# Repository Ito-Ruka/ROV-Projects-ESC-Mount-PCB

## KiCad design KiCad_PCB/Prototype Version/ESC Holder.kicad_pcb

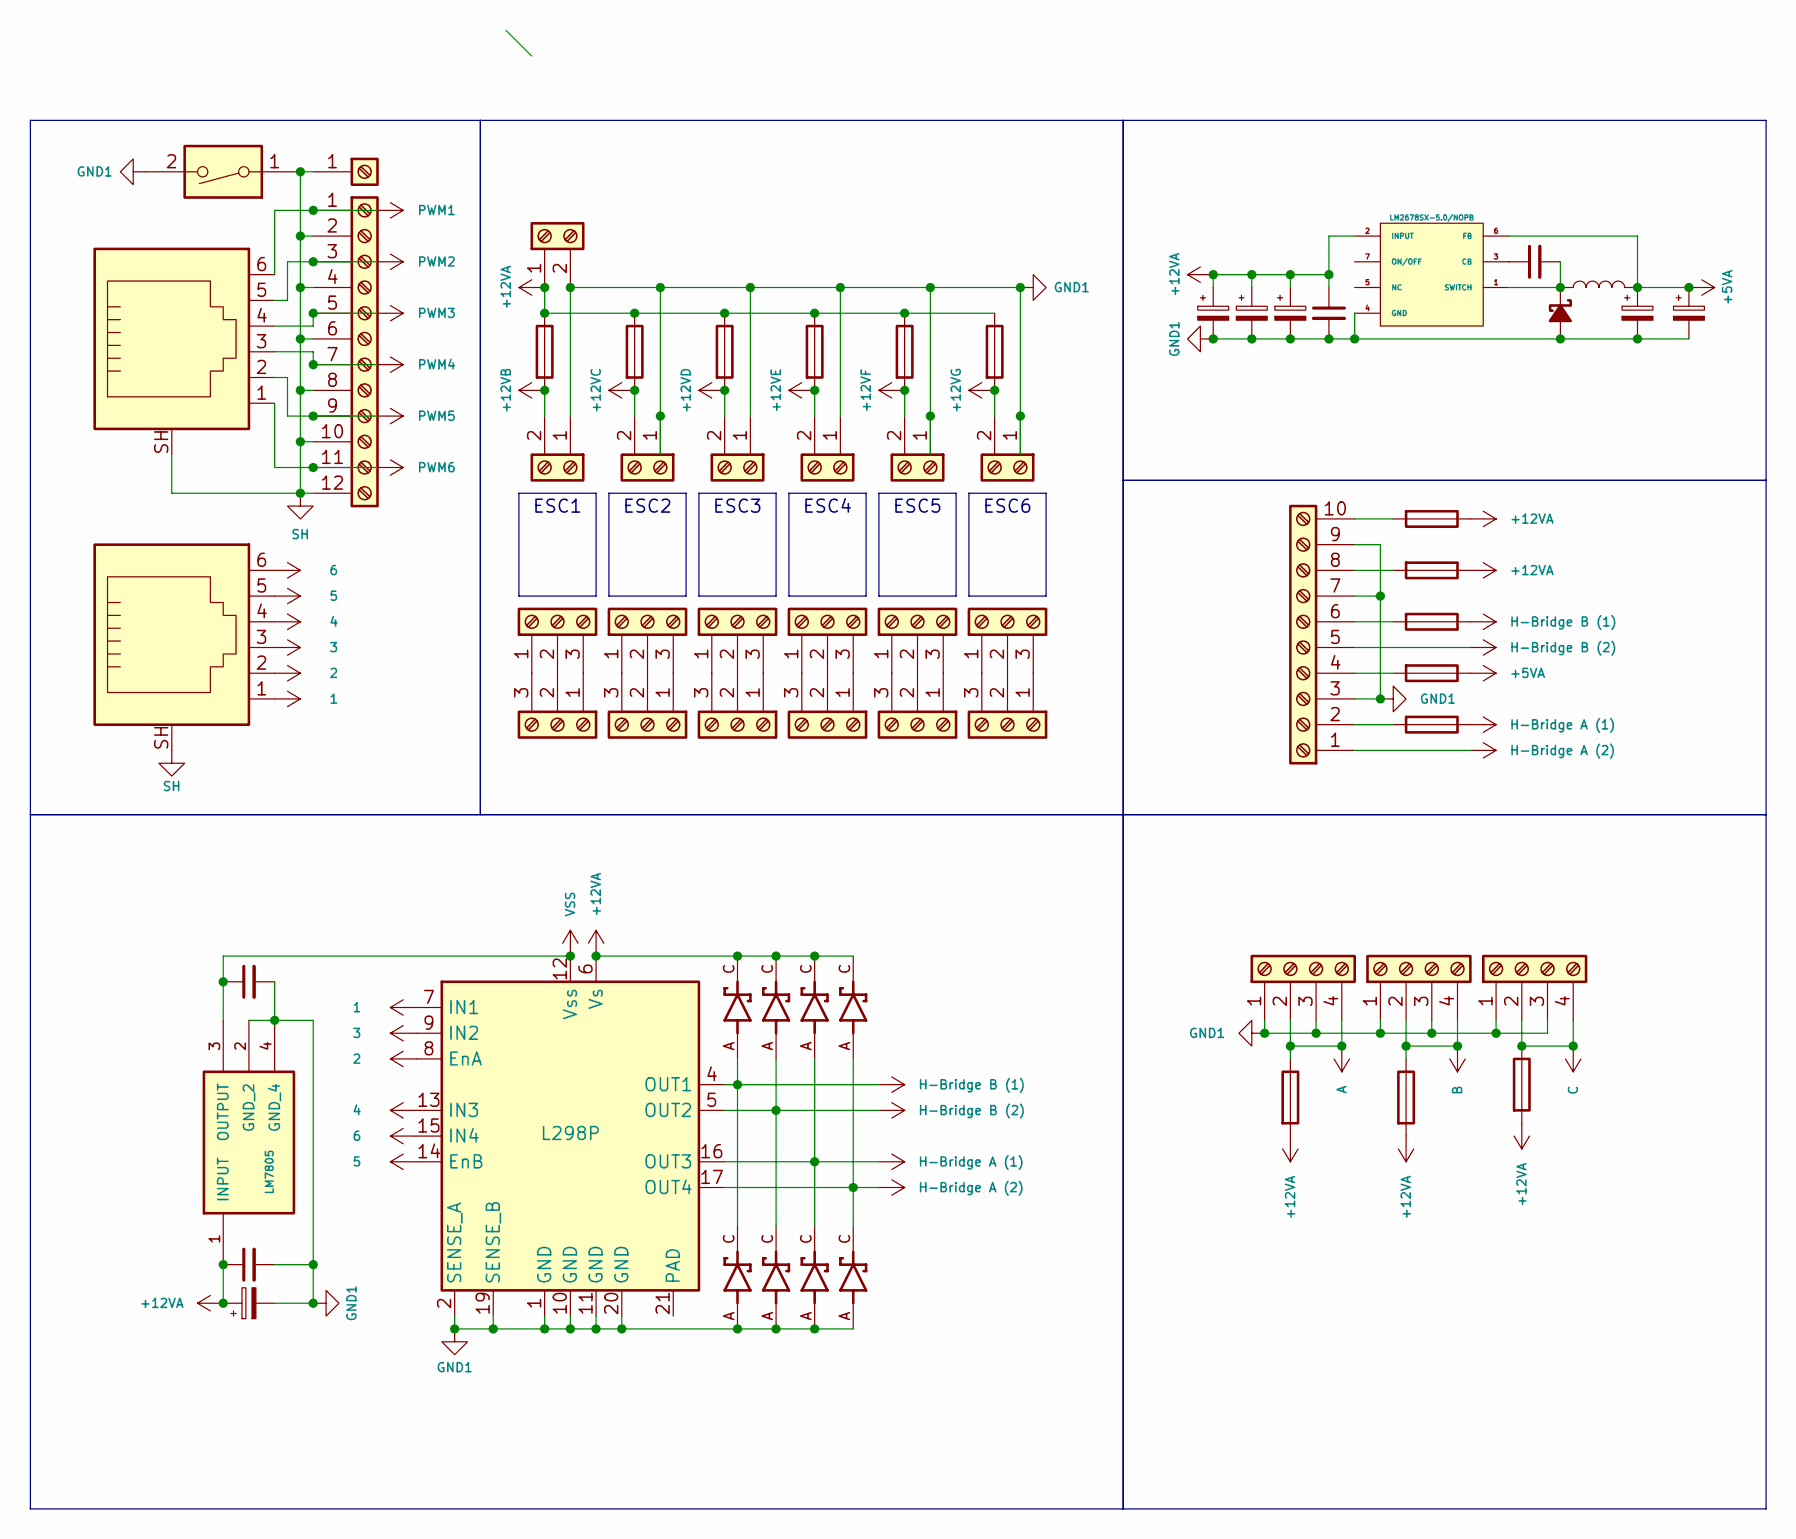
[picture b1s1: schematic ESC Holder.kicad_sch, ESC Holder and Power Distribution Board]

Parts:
C1, C2, C3: C_Polarized_Small; (15uF, 50V)WCAP-ASLI_6.3X5.5_DXL_
C4: C_Small; (0.01uF, 63V)CAPC17595_87N_KEM
C5: C_Polarized_Small; (CAP ALUM 10UF 20 25V SMD) PCAP_5x5.4-ELECT_NCA-M
C6, C8: C_Polarized_Small; (180uF, 16V) WCAP-PSLC_8X11.7_DXL_
C7: C_Small; (0.47 µF ±10 25V Ceramic Capacitor X5R 0402 (1005 Metric))C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
C9: C_Small; (CAP CER 0.1UF 25V X7R 0805) CAP_X7R_0805_AVX-M
C10: C_Small; (CAP CER 0.33UF 25V X7R 0603) WCAP-CSGP_0603_R
D1, D3, D4, D6, D7, D8, D9, D10: (DIODE SCHOTTKY 40V 3A DO214AB) DIOM7959X265N
D2: D_Schottky_Small_Filled; VS6TQ045SM3
F1, F2, F3, F4, F5, F6, F7, F8, F9, F10, F11, F12, F13, F14: Fuse; Fuse Holder 30 A 500V 1 Circuit Blade (FUSE_3568-15)
J1, J6, J9, J12, J15, J18, J22: Screw_Terminal_01x02; 2 Position Wire to Board Terminal Block Horizontal with Boa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
J2, J3, J4, J5, J7, J8, J10, J11, J13, J14, J16, J17: Screw_Terminal_01x03; 3 Position Wire to Board Terminal Block Horizontal with Boa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
J19, J21: RJ12_Shielded; Jack Modular Connector 6p6c (RJ11, RJ12, RJ14, RJ25) 90° An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
J20: Screw_Terminal_01x10; 10 Position Wire to Board Terminal Block Horizontal with Bo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
J23, J25, J26: Screw_Terminal_01x04; TERM BLK 4POS SIDE ENTRY 5MM SMD (CONN4_710304_WRE)
J24: Screw_Terminal_01x12; 12 Position Wire to Board Terminal Block Vertical with Boar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
J27: Screw_Terminal_01x01; 1 Position Wire to Board Terminal Block Horizontal with Boa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
L1: L; (22uH, 5A) IND_ETQP4M220KVC
SW1: SW_DIP_x01; SWITCH SLIDE DIP SPST 0.025A 24V (SW_A6TN-1104_OMR)
U1: TO127P1435X464-8N
U2: L298P; HSOP-20-1EP_11.0x15.9mm_P1.27mm_SlugDown
VR1: LM7805; VREG_LM7805MPX_NOPB; PARTREV L

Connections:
1: J21.1, U2.7 (IN1)
2: J21.2, U2.8 (EnA)
3: J21.3, U2.9 (IN2)
4: J21.4, U2.13 (IN3)
5: J21.5, U2.14 (EnB)
6: J21.6, U2.15 (IN4)
+5VA: C6.1, C8.1, F2.1, L1.2, U1.6 (FB)
+12VA: C1.1, C2.1, C3.1, C5.1, C7.1, C10.1, D1.C, D3.C, D4.C, D10.C, F1.1, F3.1, F5.1, F6.1, F7.1, F8.1, F10.1, F11.1, F12.2, F13.2, F14.2, J22.1, U1.2 (INPUT), U2.6 (Vs), VR1.1 (INPUT)
+12VB: F10.2, J1.2
+12VC: F1.2, J6.2
+12VD: F11.2, J9.2
+12VE: F7.2, J12.2
+12VF: F8.2, J15.2
+12VG: F6.2, J18.2
A: F12.1, J23.2, J23.4
B: F13.1, J25.2, J25.4
C: F14.1, J26.2, J26.4
GND1: C1.2, C2.2, C3.2, C5.2, C6.2, C7.2, C8.2, C9.2, C10.2, D2.2 (A), D6.A, D7.A, D8.A, D9.A, J1.1, J6.1, J9.1, J12.1, J15.1, J18.1, J20.3, J20.7, J20.9, J22.2, J23.1, J23.3, J25.1, J25.3, J26.1, J26.3, SW1.2, U1.4 (GND), U2.1 (GND), U2.2 (SENSE_A), U2.10 (GND), U2.11 (GND), U2.19 (SENSE_B), U2.20 (GND), VR1.2 (GND_2), VR1.4 (GND_4)
H-Bridge A (1): D4.A, D6.C, F4.1, U2.16 (OUT3)
H-Bridge A (2): D9.C, D10.A, J20.1, U2.17 (OUT4)
H-Bridge B (1): D1.A, D8.C, F9.1, U2.4 (OUT1)
H-Bridge B (2): D3.A, D7.C, J20.5, U2.5 (OUT2)
unnamed: C4.2, D2.1 (K), L1.1, U1.1 (SWITCH)
unnamed: J2.1, J3.3
unnamed: J2.2, J3.2
unnamed: J2.3, J3.1
unnamed: J4.1, J5.3
unnamed: J4.2, J5.2
unnamed: J4.3, J5.1
unnamed: J7.1, J8.3
unnamed: J7.2, J8.2
unnamed: J7.3, J8.1
unnamed: J10.1, J11.3
unnamed: J10.2, J11.2
unnamed: J10.3, J11.1
unnamed: J13.1, J14.3
unnamed: J13.2, J14.2
unnamed: J13.3, J14.1
unnamed: J16.1, J17.3
unnamed: J16.2, J17.2
unnamed: J16.3, J17.1
unnamed: F4.2, J20.2
unnamed: F2.2, J20.4
unnamed: F9.2, J20.6
unnamed: F5.2, J20.8
unnamed: F3.2, J20.10
unnamed: C4.1, U1.3 (CB)
PWM1: J19.6, J24.1
PWM2: J19.5, J24.3
PWM3: J19.4, J24.5
PWM4: J19.3, J24.7
PWM5: J19.2, J24.9
PWM6: J19.1, J24.11
SH: J19.SH, J21.SH, J24.2, J24.4, J24.6, J24.8, J24.10, J24.12, J27.1, SW1.1
VSS: C9.1, U2.12 (Vss), VR1.3 (OUTPUT)

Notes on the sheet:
ESC4
ESC1
ESC3
ESC2
ESC6
ESC5

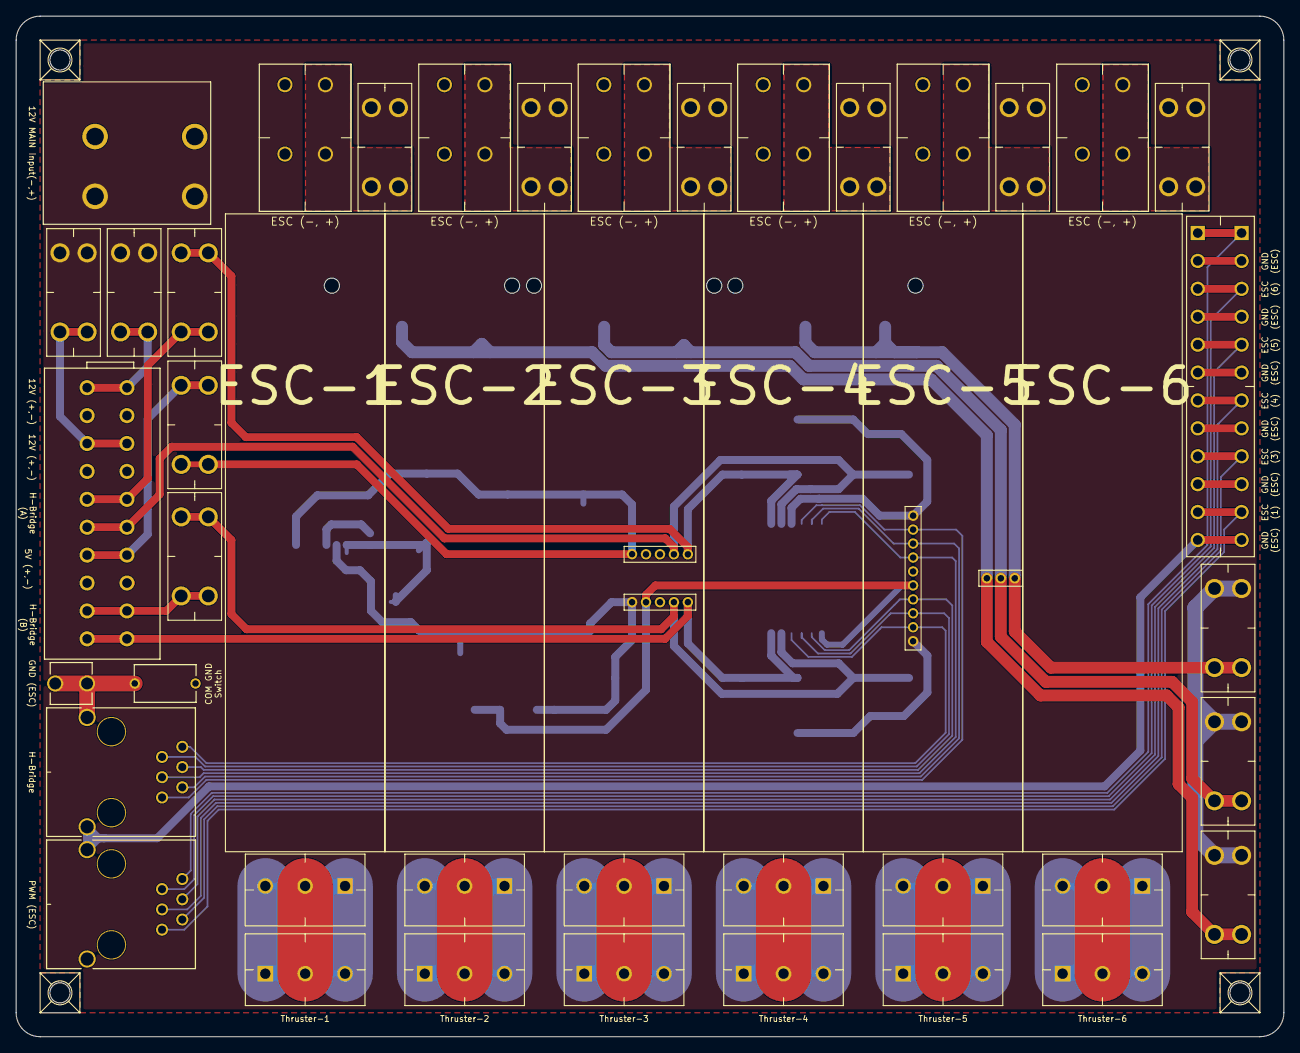
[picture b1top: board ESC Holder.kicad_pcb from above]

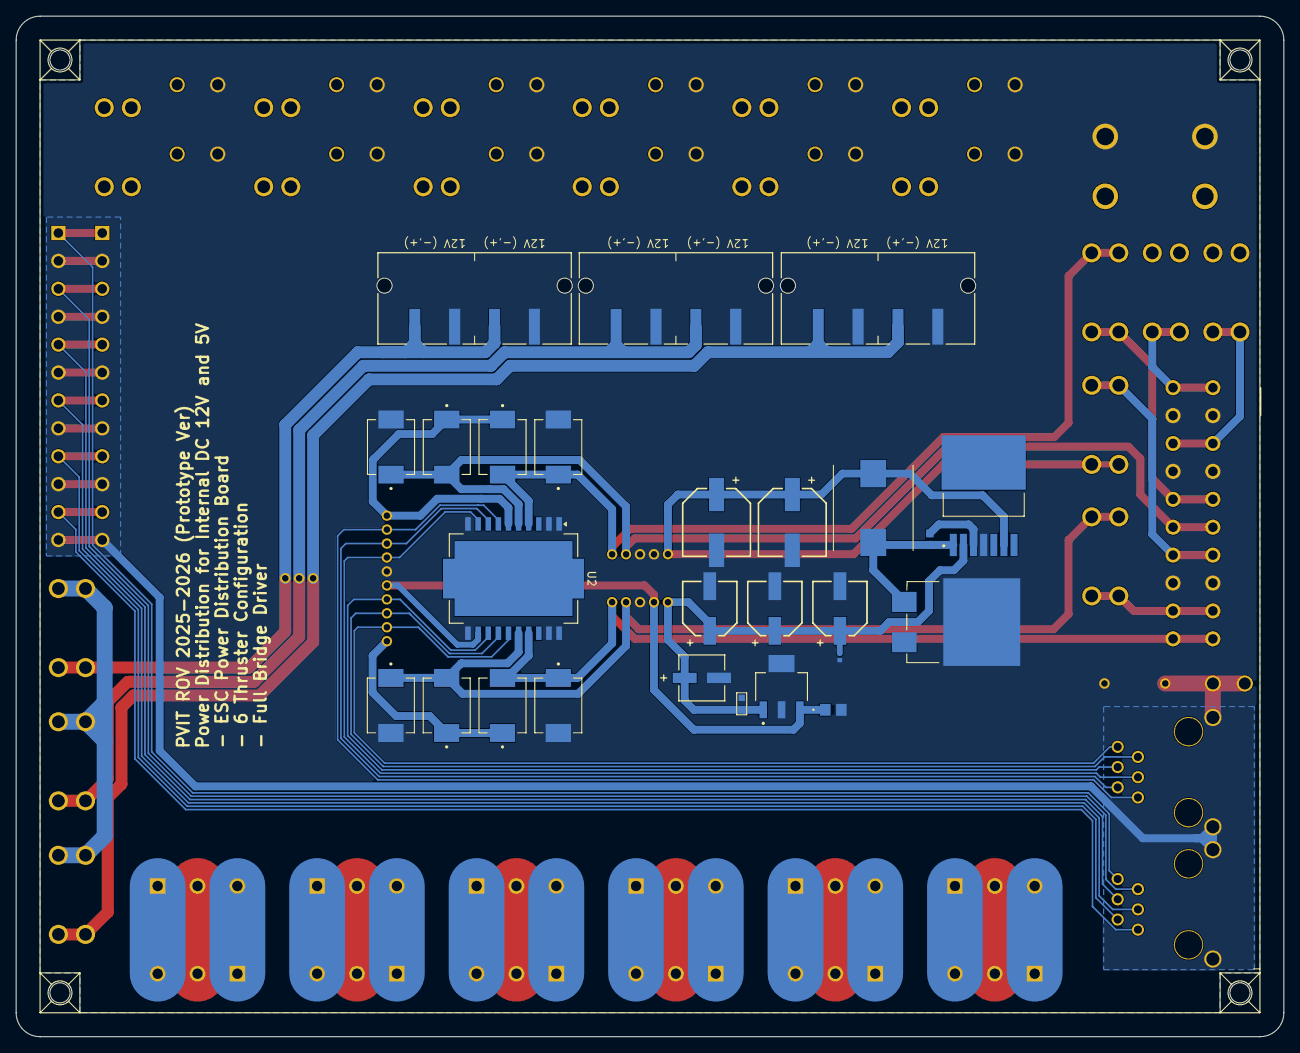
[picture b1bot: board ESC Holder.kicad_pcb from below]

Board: 2 copper layers, 159.0 x 128.0 mm, 65 parts (26 on the bottom side), 55 nets.
